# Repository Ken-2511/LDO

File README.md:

# Stackable BLE low-noise power supply (PoC)

Two KiCad 10 projects, stacked on the same 40x40 mm footprint:

- `controller/`: Seeed XIAO nRF52840 board at the bottom of the stack. It supplies 5V (from USB) and 3.3V, and carries the I2C pull-ups.
- `ldo/`: LDO board, one LT3042 channel set by a DAC60502 and read back by an INA226. Up to 4 boards stack on the controller, each on its own I2C address.

The boards connect through a 2x5 stacking header (J1) at the same position on every board:
pins 1-2 +5V, pin 3 +3V3, pin 5 SDA, pin 7 SCL, pins 4, 6, 8, 9, 10 GND.

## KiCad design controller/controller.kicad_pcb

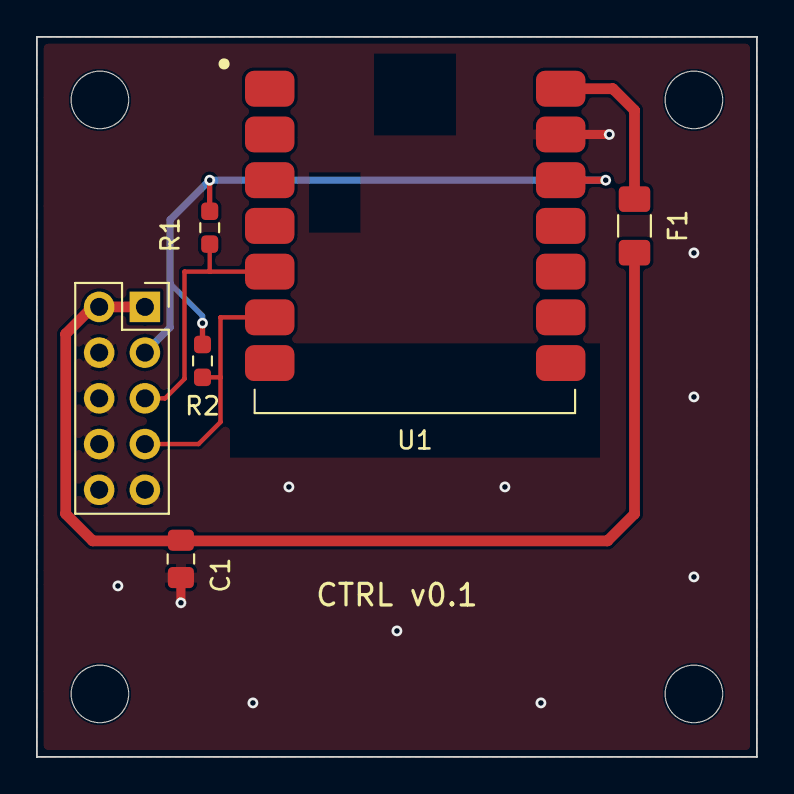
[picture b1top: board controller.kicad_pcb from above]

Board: 2 copper layers, 40.0 x 40.0 mm, 10 parts (0 on the bottom side), 6 nets.

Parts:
C1: 10uF 25V; C_0805_2012Metric_Pad1.18x1.45mm_HandSolder
F1: 500mA; Fuse_1206_3216Metric_Pad1.42x1.75mm_HandSolder
H1, H2, H3, H4: M3; MountingHole_3.2mm_M3
J1: Stack_2x05; PinSocket_2x05_P2.54mm_Vertical
R1, R2: 4.7k; R_0603_1608Metric_Pad0.98x0.95mm_HandSolder
U1: XIAO_nRF52840; XIAO_nRF52840_SMD

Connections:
+3V3: J1.3, R1.1, R2.1, U1.12
+5V: C1.1, F1.2, J1.1, J1.2
/SCL: J1.7, R2.2, U1.6
/SDA: J1.5, R1.2, U1.5
/VBUS: F1.1, U1.14
GND: C1.2, J1.4, J1.6, J1.8, J1.9, J1.10, U1.13

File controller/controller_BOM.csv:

"Comment","Qty","Designator","Footprint","MPN","LCSC Part #"
"10uF 25V","1","C1","Capacitor_SMD:C_0805_2012Metric_Pad1.18x1.45mm_HandSolder","CL21A106KAYNNNE","C15850"
"500mA","1","F1","Fuse:Fuse_1206_3216Metric_Pad1.42x1.75mm_HandSolder","MF-NSMF050-2","C75464"
"Stack_2x05","1","J1","Connector_PinSocket_2.54mm:PinSocket_2x05_P2.54mm_Vertical","PM254V-12-10P-H85","C492399"
"4.7k","2","R1,R2","Resistor_SMD:R_0603_1608Metric_Pad0.98x0.95mm_HandSolder","0603WAF4701T5E","C23162"
"XIAO_nRF52840","1","U1","controller:XIAO_nRF52840_SMD","Seeed XIAO nRF52840",""

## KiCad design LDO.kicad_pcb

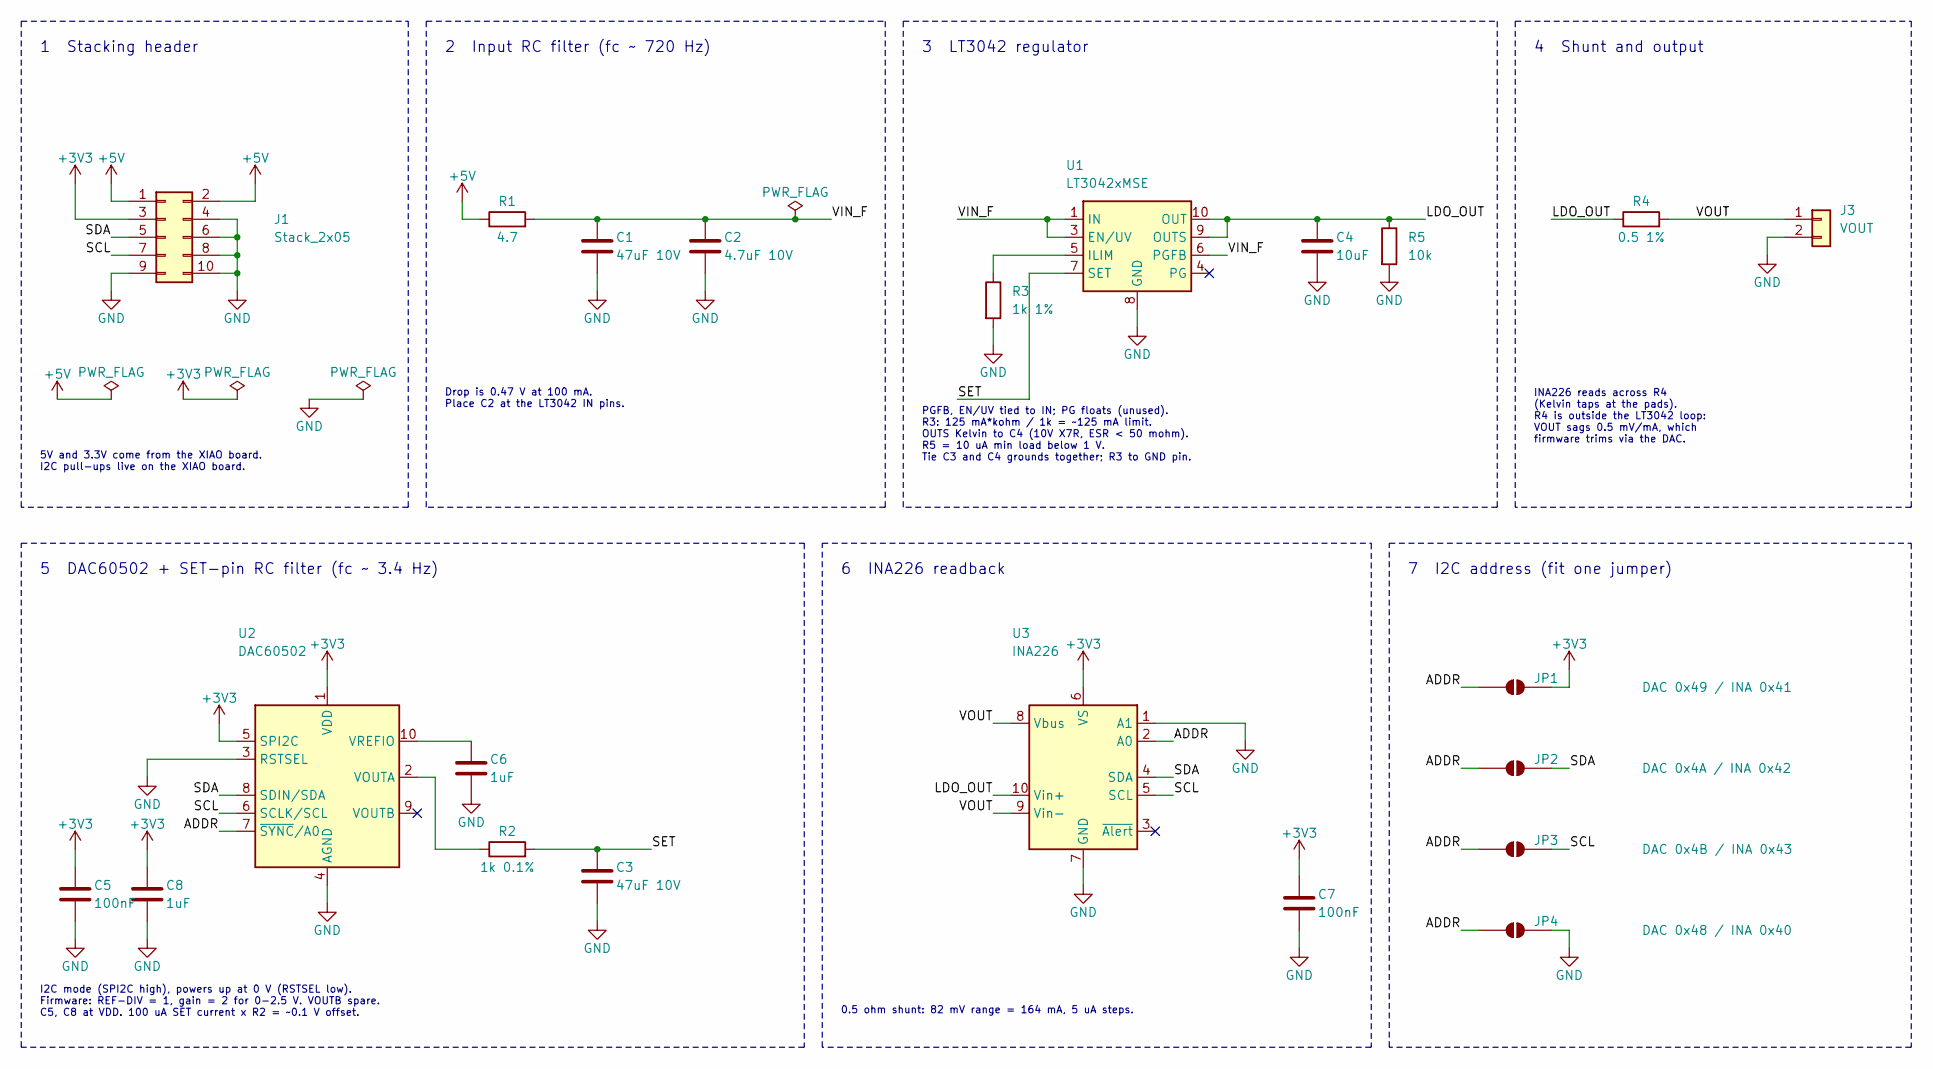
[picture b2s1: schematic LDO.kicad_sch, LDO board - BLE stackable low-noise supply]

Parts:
C1, C3: 47uF 10V; C_1206_3216Metric_Pad1.33x1.80mm_HandSolder; MPN CL31A476MPHNNNE; LCSC C96123
C2: 4.7uF 10V; C_0805_2012Metric_Pad1.18x1.45mm_HandSolder; MPN CL21B475KAFNNNE; LCSC C98195
C4: 10uF; C_0805_2012Metric_Pad1.18x1.45mm_HandSolder; MPN CL21A106KAYNNNE; LCSC C15850
C5, C7: 100nF; C_0603_1608Metric_Pad1.08x0.95mm_HandSolder; MPN CL10B104KB8NNNC; LCSC C1591
C6, C8: 1uF; C_0603_1608Metric_Pad1.08x0.95mm_HandSolder; MPN CL10B105KA8NNNC; LCSC C29936
J1: Stack_2x05; PinSocket_2x05_P2.54mm_Vertical
J3: VOUT; PinHeader_1x02_P2.54mm_Horizontal; MPN PZ254R-11-02P; LCSC C492410
JP1: DAC 0x49 / INA 0x41; SolderJumper-2_P1.3mm_Open_RoundedPad1.0x1.5mm
JP2: DAC 0x4A / INA 0x42; SolderJumper-2_P1.3mm_Open_RoundedPad1.0x1.5mm
JP3: DAC 0x4B / INA 0x43; SolderJumper-2_P1.3mm_Open_RoundedPad1.0x1.5mm
JP4: DAC 0x48 / INA 0x40; SolderJumper-2_P1.3mm_Open_RoundedPad1.0x1.5mm
R1: 4.7; R_0805_2012Metric_Pad1.20x1.40mm_HandSolder; MPN SR0805FR-7W4R7L; LCSC C873778
R2: 1k 0.1%; R_0603_1608Metric_Pad0.98x0.95mm_HandSolder; MPN RT0603BRD071KL; LCSC C110776
R3: 1k 1%; R_0603_1608Metric_Pad0.98x0.95mm_HandSolder; MPN 0603WAF1001T5E; LCSC C21190
R4: 0.5 1%; R_1206_3216Metric_Pad1.30x1.75mm_HandSolder; MPN RL1206FR-070R5L; LCSC C327075
R5: 10k; R_0603_1608Metric_Pad0.98x0.95mm_HandSolder; MPN 0603WAF1002T5E; LCSC C25804
U1: LT3042xMSE; MSOP-10-1EP_3x3mm_P0.5mm_EP1.68x1.88mm; MPN LT3042EMSE#PBF; LCSC C69847
U2: DAC60502; Texas_DRX_WSON-10_2.5x2.5mm_P0.5mm; MPN DAC60502DRXR; LCSC C2876322
U3: INA226; TSSOP-10_3x3mm_P0.5mm; MPN INA226AIDGSR; LCSC C49851

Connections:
+3V3: C5.1, C7.1, C8.1, J1.3, JP1.2 (B), U2.1 (VDD), U2.5 (SPI2C), U3.6 (VS)
+5V: J1.1, J1.2, R1.1
/ADDR: JP1.1 (A), JP2.1 (A), JP3.1 (A), JP4.1 (A), U2.7 (~SYNC/A0), U3.2 (A0)
/LDO_OUT: C4.1, R4.1, R5.1, U1.9 (OUTS), U1.10 (OUT), U3.10 (Vin+)
/SCL: J1.7, JP3.2 (B), U2.6 (SCLK/SCL), U3.5 (SCL)
/SDA: J1.5, JP2.2 (B), U2.8 (SDIN/SDA), U3.4 (SDA)
/SET: C3.1, R2.2, U1.7 (SET)
/VIN_F: C1.1, C2.1, R1.2, U1.1 (IN), U1.2 (IN), U1.3 (EN/UV), U1.6 (PGFB)
/VOUT: J3.1, R4.2, U3.8 (Vbus), U3.9 (Vin-)
GND: C1.2, C2.2, C3.2, C4.2, C5.2, C6.2, C7.2, C8.2, J1.4, J1.6, J1.8, J1.9, J1.10, J3.2, JP4.2 (B), R3.2, R5.2, U1.8 (GND), U1.11 (GND), U2.3 (RSTSEL), U2.4 (AGND), U3.1 (A1), U3.7 (GND)
unnamed: R3.1, U1.5 (ILIM)
unnamed: R2.1, U2.2 (VOUTA)
unnamed: C6.1, U2.10 (VREFIO)

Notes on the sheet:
1 Stacking header
5V and 3.3V come from the XIAO board. I2C pull-ups live on the XIAO board.
2 Input RC filter (fc ~ 720 Hz)
Drop is 0.47 V at 100 mA. Place C2 at the LT3042 IN pins.
3 LT3042 regulator
PGFB, EN/UV tied to IN; PG floats (unused). R3: 125 mA*kohm / 1k = ~125 mA limit. OUTS Kelvin to C4 (10V X7R, ESR < 50 mohm). R5 = 10 uA min load below 1 V. Tie C3 and C4 grounds together; R3 to GND pin.
4 Shunt and output
INA226 reads across R4 (Kelvin taps at the pads). R4 is outside the LT3042 loop: VOUT sags 0.5 mV/mA, which firmware trims via the DAC.
5 DAC60502 + SET-pin RC filter (fc ~ 3.4 Hz)
I2C mode (SPI2C high), powers up at 0 V (RSTSEL low). Firmware: REF-DIV = 1, gain = 2 for 0-2.5 V. VOUTB spare. C5, C8 at VDD. 100 uA SET current x R2 = ~0.1 V offset.
6 INA226 readback
0.5 ohm shunt: 82 mV range = 164 mA, 5 uA steps.
7 I2C address (fit one jumper)

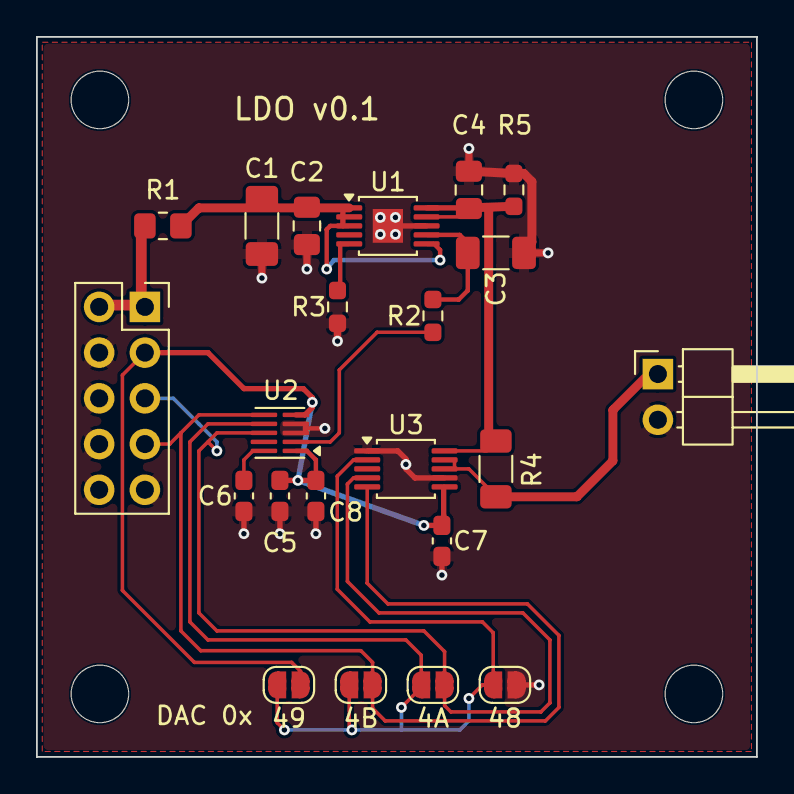
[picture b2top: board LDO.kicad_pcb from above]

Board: 2 copper layers, 40.0 x 40.0 mm, 26 parts (0 on the bottom side), 13 nets.

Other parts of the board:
H1, H2, H3, H4: M3; MountingHole_3.2mm_M3

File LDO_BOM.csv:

"Comment","Qty","Designator","Footprint","MPN","LCSC Part #"
"47uF 10V","2","C1,C3","Capacitor_SMD:C_1206_3216Metric_Pad1.33x1.80mm_HandSolder","CL31A476MPHNNNE","C96123"
"4.7uF 10V","1","C2","Capacitor_SMD:C_0805_2012Metric_Pad1.18x1.45mm_HandSolder","CL21B475KAFNNNE","C98195"
"10uF","1","C4","Capacitor_SMD:C_0805_2012Metric_Pad1.18x1.45mm_HandSolder","CL21A106KAYNNNE","C15850"
"100nF","2","C5,C7","Capacitor_SMD:C_0603_1608Metric_Pad1.08x0.95mm_HandSolder","CL10B104KB8NNNC","C1591"
"1uF","2","C6,C8","Capacitor_SMD:C_0603_1608Metric_Pad1.08x0.95mm_HandSolder","CL10B105KA8NNNC","C29936"
"Stack_2x05","1","J1","Connector_PinSocket_2.54mm:PinSocket_2x05_P2.54mm_Vertical","",""
"VOUT","1","J3","Connector_PinHeader_2.54mm:PinHeader_1x02_P2.54mm_Horizontal","PZ254R-11-02P","C492410"
"4.7","1","R1","Resistor_SMD:R_0805_2012Metric_Pad1.20x1.40mm_HandSolder","SR0805FR-7W4R7L","C873778"
"1k 0.1%","1","R2","Resistor_SMD:R_0603_1608Metric_Pad0.98x0.95mm_HandSolder","RT0603BRD071KL","C110776"
"1k 1%","1","R3","Resistor_SMD:R_0603_1608Metric_Pad0.98x0.95mm_HandSolder","0603WAF1001T5E","C21190"
"0.5 1%","1","R4","Resistor_SMD:R_1206_3216Metric_Pad1.30x1.75mm_HandSolder","RL1206FR-070R5L","C327075"
"10k","1","R5","Resistor_SMD:R_0603_1608Metric_Pad0.98x0.95mm_HandSolder","0603WAF1002T5E","C25804"
"LT3042xMSE","1","U1","Package_SO:MSOP-10-1EP_3x3mm_P0.5mm_EP1.68x1.88mm","LT3042EMSE#PBF","C69847"
"DAC60502","1","U2","Package_SON:Texas_DRX_WSON-10_2.5x2.5mm_P0.5mm","DAC60502DRXR","C2876322"
"INA226","1","U3","Package_SO:TSSOP-10_3x3mm_P0.5mm","INA226AIDGSR","C49851"
